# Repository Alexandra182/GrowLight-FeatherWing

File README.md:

# GrowLight-FeatherWing 🌞

🌱 A minimalist grow light that is compatible with the Adafruit Feather Huzzah dev board.

🌱 For more details check out [Hackster](https://hackaday.io/project/177078-grow-light-feather-wing).

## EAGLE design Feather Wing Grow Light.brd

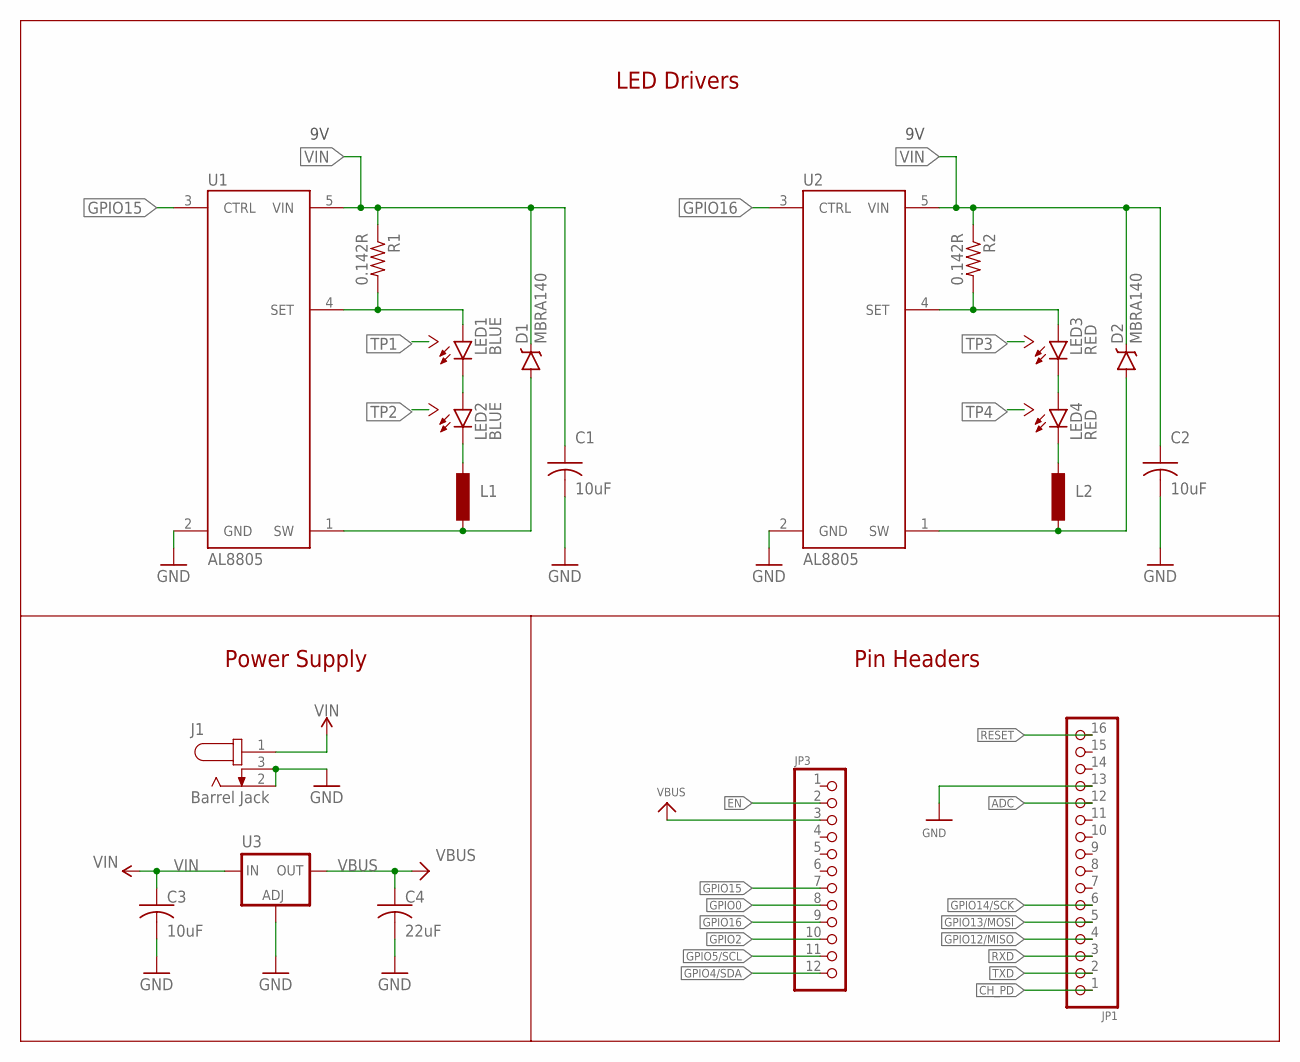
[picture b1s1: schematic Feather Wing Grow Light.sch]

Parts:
C1, C2, C3: 10uF; C0805
C4: 22uF; C0805
D1, D2: MBRA140; SMA-DIODE
J1: Barrel Jack; CUI_PJ-014D
JP1: HEADER-1X16ROUND; 1X16_ROUND
JP3: HEADER-1X12; 1X12_ROUND
L1: 33uH; 0207/10
L2: 3.3µH/±30%/3.4A; 0207/10
LED1, LED2: BLUE; CREE_XLAMP
LED3, LED4: RED; CREE_XLAMP
R1, R2: 0.142R; 0805
U1, U2: AL8805; SOT23-5
U3: LM1117SOT223-REFLOW; SOT223-R

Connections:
ADC: JP1.12
CH_PD: JP1.1
EN: JP3.2
GND: C1.2, C2.2, C3.2, C4.2, J1.2, J1.3, JP1.13, U1.2 (GND), U2.2 (GND), U3.1 (ADJ)
GPIO0: JP3.8
GPIO2: JP3.10
GPIO4/SDA: JP3.12
GPIO5/SCL: JP3.11
GPIO12/MISO: JP1.4
GPIO13/MOSI: JP1.5
GPIO14/SCK: JP1.6
GPIO15: JP3.7, U1.3 (CTRL)
GPIO16: JP3.9, U2.3 (CTRL)
unnamed: LED3.C, LED3.C@1 (C), LED4.A, LED4.A@1 (A)
unnamed: LED1.C, LED1.C@1 (C), LED2.A, LED2.A@1 (A)
unnamed: L1.2, LED2.C, LED2.C@1 (C)
unnamed: L2.2, LED4.C, LED4.C@1 (C)
OUT+1: LED3.A, LED3.A@1 (A), R2.2, U2.4 (SET)
OUT+2: LED1.A, LED1.A@1 (A), R1.2, U1.4 (SET)
RESET: JP1.16
RXD: JP1.3
SW1: D2.A, L2.1, U2.1 (SW)
SW2: D1.A, L1.1, U1.1 (SW)
TP1: LED1.X
TP2: LED2.X
TP3: LED3.X
TP4: LED4.X
TXD: JP1.2
VBUS: C4.1, JP3.3, U3.2 (OUT)
VIN: C1.1, C2.1, C3.1, D1.C, D2.C, J1.1, R1.1, R2.1, U1.5 (VIN), U2.5 (VIN), U3.3 (IN)

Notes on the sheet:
Power Supply
Pin Headers
LED Drivers

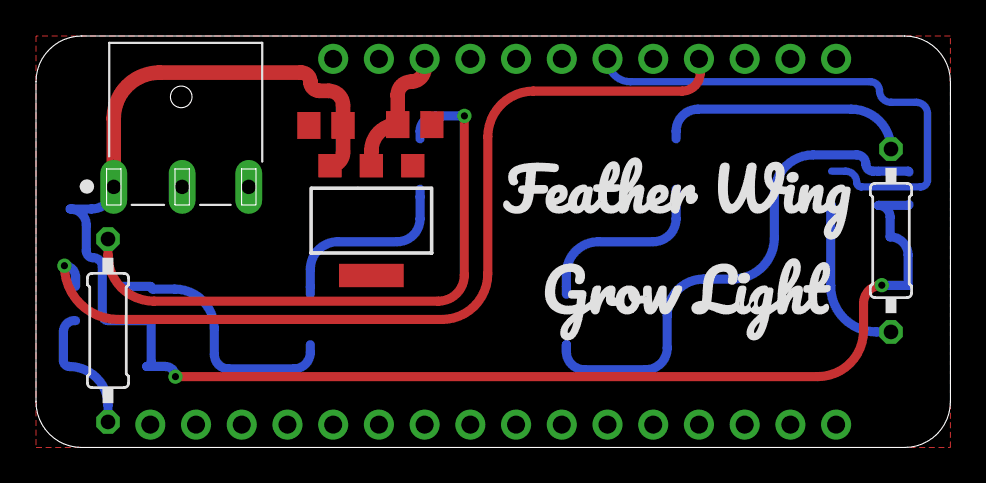
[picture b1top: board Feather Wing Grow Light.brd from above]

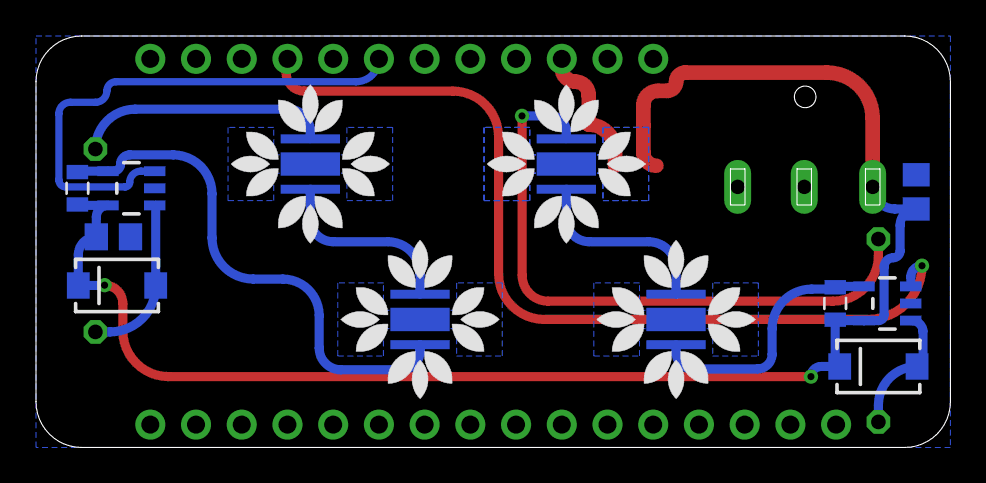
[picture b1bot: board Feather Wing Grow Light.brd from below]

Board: 2 copper layers, 50.8 x 22.9 mm, 20 parts (12 on the bottom side), 13 nets.

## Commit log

2021-02-21 Added Adafruit IO code
2021-02-21 cleanup
2021-02-21 timer code

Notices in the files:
parts and their libraries:
microbuilder: This work is placed in the public domain, and may be freely used for commercial and non-commercial work with the following conditions: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
SparkFun-PowerIC: Licensing: CC v3.0 Share-Alike You are welcome to use this library for commercial purposes.
